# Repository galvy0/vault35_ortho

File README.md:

# Vault35 Ortho PCB
Ortho version of Cain's Vault35 keyboard.  
Check out the original product and other awesome projects of Cain at [https://mechvault.net/](https://mechvault.net/).  

### Current Progress
PCB has been tested and is good to go.  
Now working on plates.  

## PCB
### PCB Renders

### Layout Options

## Plate
Many plate configurations are possible depending on the use of the middle column.  
Various plate options can be found in plates folder.  
This is the most inclusive version, which supports every configuration except 3u stabs on macro column:  

## Firmware
https://github.com/galvy0/qmk_firmware/tree/galvy/keyboards/galvy/vault35_ortho

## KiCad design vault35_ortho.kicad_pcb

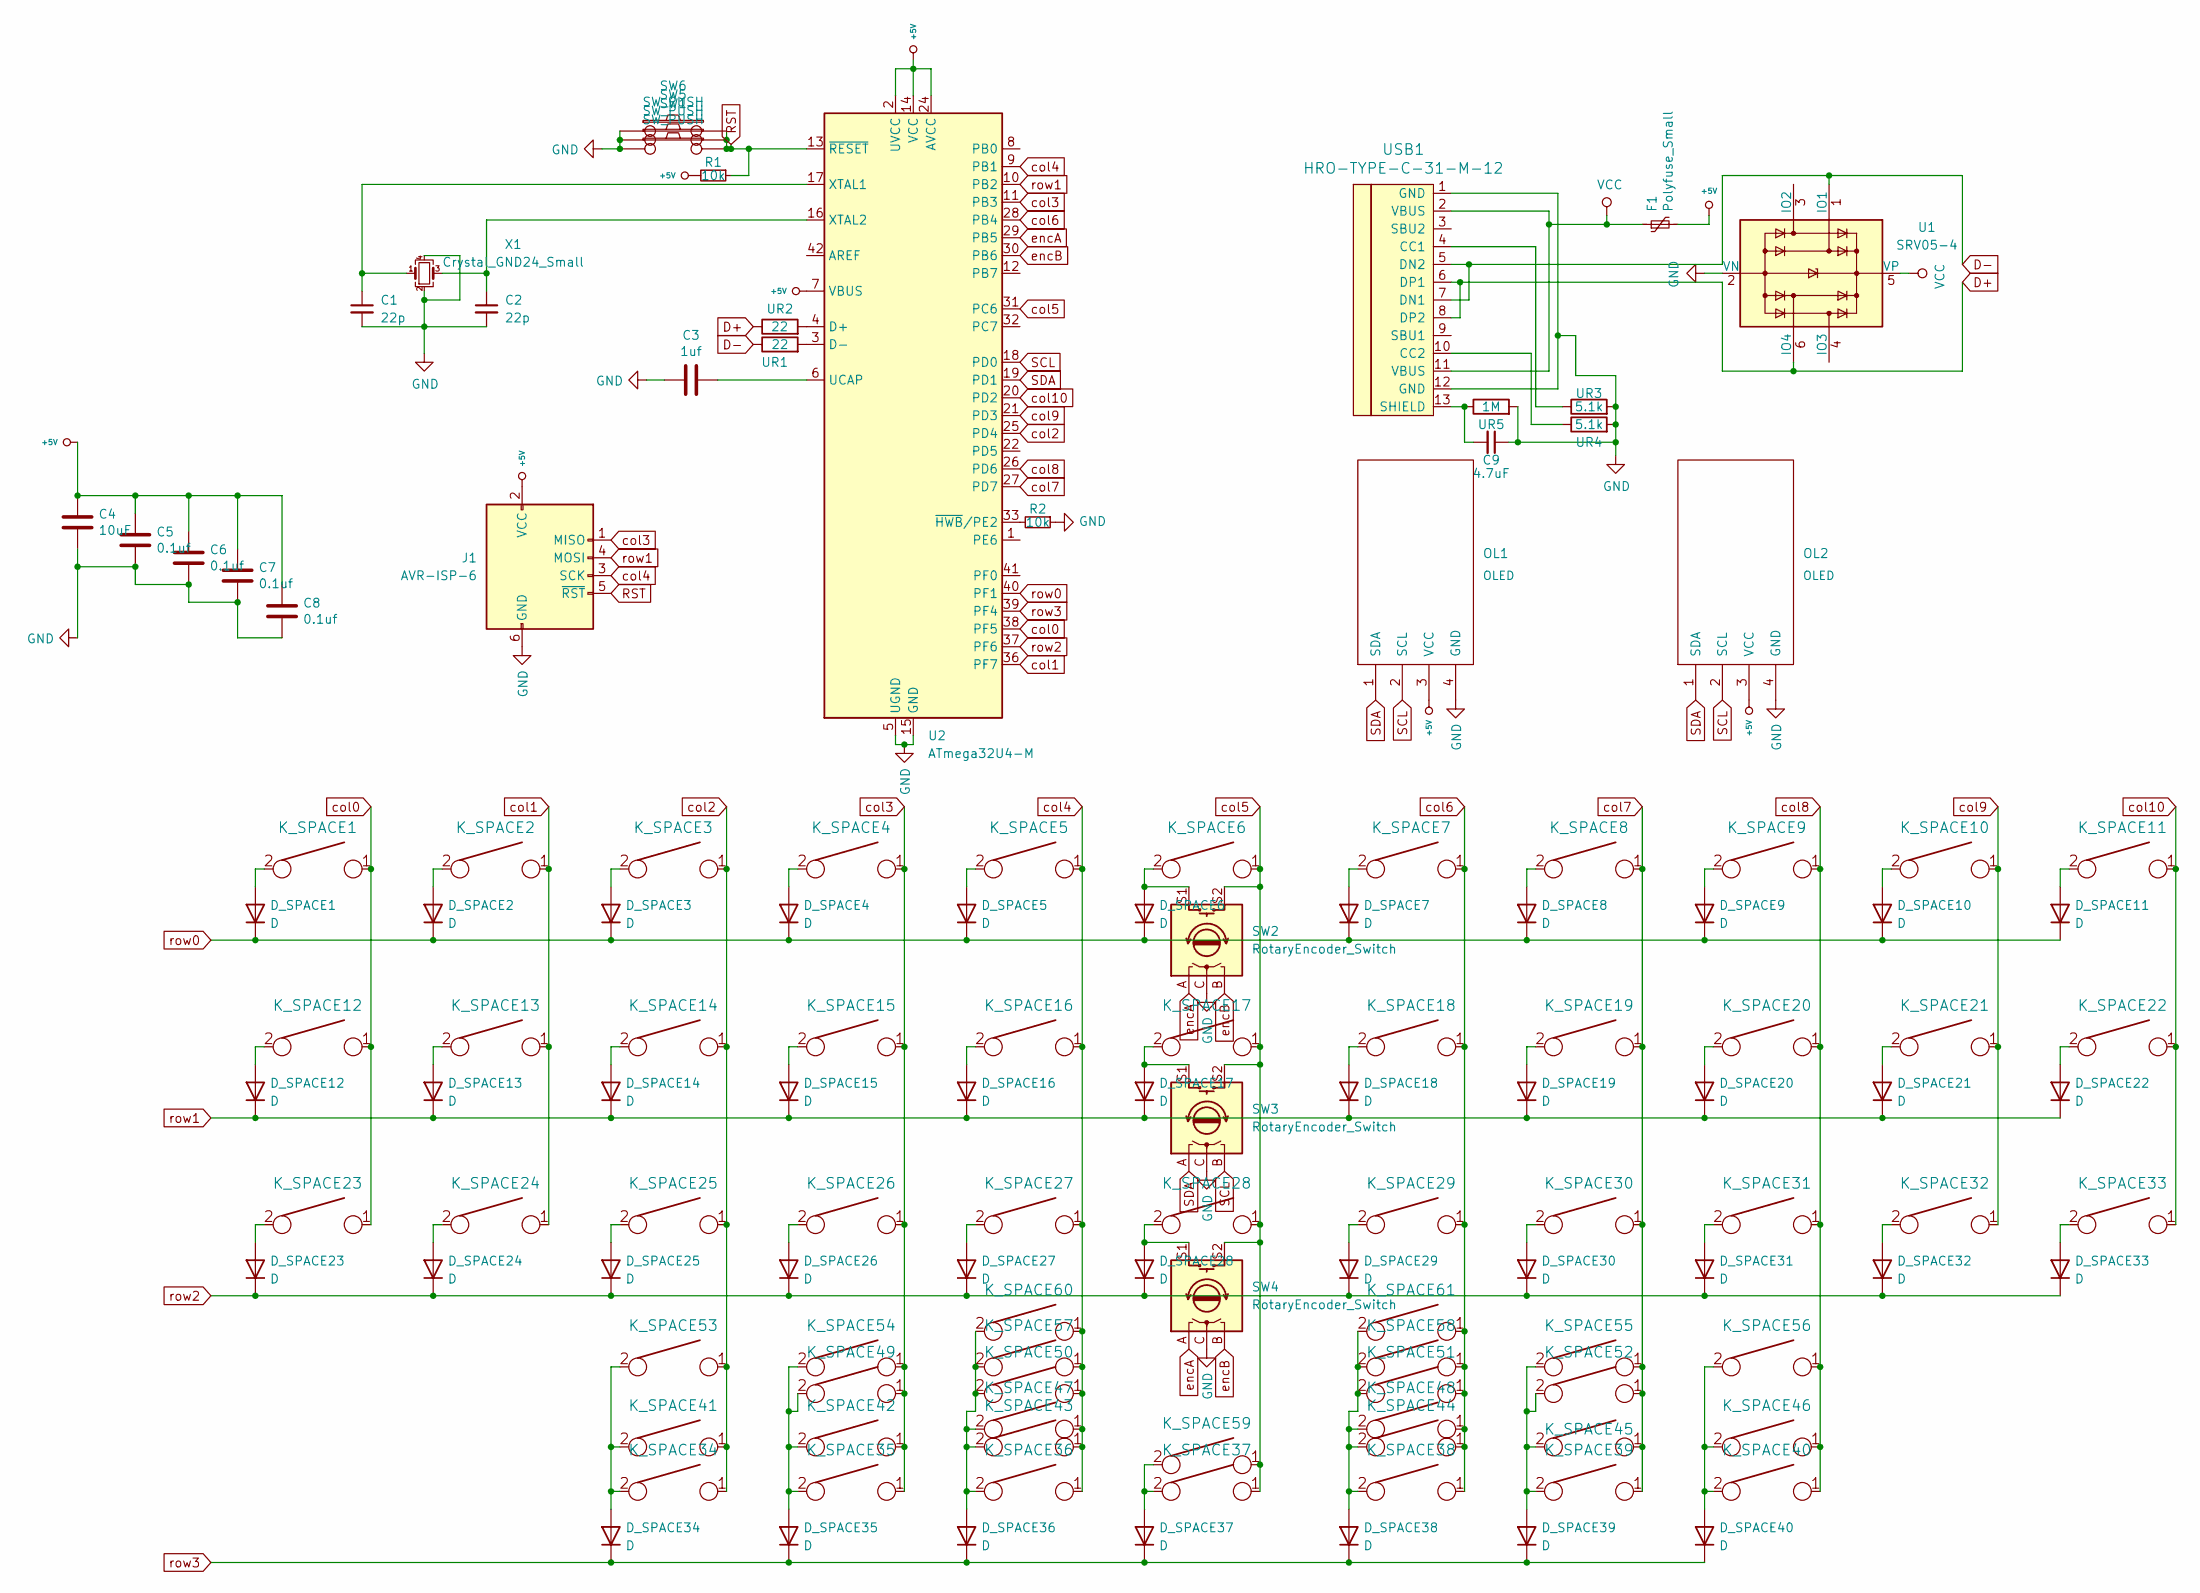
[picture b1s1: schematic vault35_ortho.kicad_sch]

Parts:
C1, C2: 22p; C_0805_2012Metric
C3: 1uf; C_0805_2012Metric
C4: 10uF; C_0805_2012Metric
C5, C6, C7, C8: 0.1uf; C_0805_2012Metric
C9: 4.7uF; C_0805_2012Metric
D_SPACE1, D_SPACE2, D_SPACE3, D_SPACE4, D_SPACE5, D_SPACE6, D_SPACE7, D_SPACE8, D_SPACE9, D_SPACE10, D_SPACE11, D_SPACE12, D_SPACE13, D_SPACE14, D_SPACE15, D_SPACE16, D_SPACE17, D_SPACE18, D_SPACE19, D_SPACE20, D_SPACE21, D_SPACE22, D_SPACE23, D_SPACE24, D_SPACE25, D_SPACE26, D_SPACE27, D_SPACE28, D_SPACE29, D_SPACE30, D_SPACE31, D_SPACE32, D_SPACE33, D_SPACE34, D_SPACE35, D_SPACE36, D_SPACE37, D_SPACE38, D_SPACE39, D_SPACE40: D; D_SOD-123
F1: Polyfuse_Small; Fuse_1206_3216Metric_Pad1.42x1.75mm_HandSolder
J1: AVR-ISP-6; IDC-Header_2x03_P2.54mm_Vertical
K_SPACE1, K_SPACE2, K_SPACE3, K_SPACE4, K_SPACE5, K_SPACE6, K_SPACE7, K_SPACE8, K_SPACE9, K_SPACE10, K_SPACE11, K_SPACE12, K_SPACE13, K_SPACE14, K_SPACE15, K_SPACE16, K_SPACE17, K_SPACE18, K_SPACE19, K_SPACE20, K_SPACE21, K_SPACE22, K_SPACE23, K_SPACE24, K_SPACE25, K_SPACE26, K_SPACE27, K_SPACE28, K_SPACE29, K_SPACE30, K_SPACE31, K_SPACE32, K_SPACE33, K_SPACE35, K_SPACE36, K_SPACE37, K_SPACE38, K_SPACE39, K_SPACE41, K_SPACE42, K_SPACE45, K_SPACE46: KEYSW; MXOnly-1U-NoLED
K_SPACE34, K_SPACE40, K_SPACE60, K_SPACE61: KEYSW; MXOnly-1.5U-NoLED
K_SPACE43, K_SPACE44: KEYSW; MXOnly-2U-ReversedStabilizers-NoLED
K_SPACE47: KEYSW; MXOnly-2.25U-ReversedStabilizers-NoLED
K_SPACE48: KEYSW; MXOnly-2.75U-ReversedStabilizers-NoLED
K_SPACE49, K_SPACE52, K_SPACE53, K_SPACE54, K_SPACE55, K_SPACE56: KEYSW; MXOnly-1.25U-NoLED
K_SPACE50, K_SPACE51: KEYSW; MXOnly-1.75U-NoLED
K_SPACE57, K_SPACE58, K_SPACE59: KEYSW; MXOnly-3U-ReversedStabilizers-NoLED
OL1, OL2: OLED; OLED_v2
R1, R2: 10k; R_0805_2012Metric
SW1, SW6: SW_PUSH; SW_SPST_SKQG_WithoutStem
SW2, SW3, SW4: RotaryEncoder_Switch; RotaryEncoder_Alps_EC11E-Switch_Vertical_H20mm
SW5: SW_PUSH; PinHeader_1x02_P2.54mm_Vertical
U1: SRV05-4; SOT-23-6
U2: ATmega32U4-M; QFN-44-1EP_7x7mm_P0.5mm_EP5.2x5.2mm
UR1, UR2: 22; R_0805_2012Metric
UR3, UR4: 5.1k; R_0805_2012Metric
UR5: 1M; R_0805_2012Metric
USB1: HRO-TYPE-C-31-M-12; HRO-TYPE-C-31-M-12-HandSoldering
X1: Crystal_GND24_Small; Crystal_SMD_3225-4Pin_3.2x2.5mm_HandSoldering

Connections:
+5V: C4.1, C5.1, C6.1, C7.1, C8.1, F1.2, J1.2 (VCC), OL1.3 (VCC), OL2.3 (VCC), R1.2, U2.2 (UVCC), U2.7 (VBUS), U2.14 (VCC), U2.24 (AVCC), U2.34 (VCC), U2.44 (AVCC)
D+: U1.6 (IO4), UR1.1, USB1.6 (DP1), USB1.8 (DP2)
D-: U1.1 (IO1), UR2.1, USB1.5 (DN2), USB1.7 (DN1)
GND: C1.2, C2.2, C3.2, C4.2, C5.2, C6.2, C7.2, C8.2, C9.1, J1.6 (GND), OL1.4 (GND), OL2.4 (GND), R2.1, SW1.1, SW2.C, SW3.C, SW4.C, SW5.1, SW6.1, U1.2 (VN), U2.5 (UGND), U2.15 (GND), U2.23 (GND), U2.35 (GND), U2.43 (GND), U2.45 (GND), UR3.2, UR4.2, UR5.2, USB1.1 (GND), USB1.12 (GND), X1.2, X1.4
unnamed: C1.1, U2.17 (XTAL1), X1.1
unnamed: C2.1, U2.16 (XTAL2), X1.3
unnamed: C3.1, U2.6 (UCAP)
unnamed: C9.2, UR5.1, USB1.13 (SHIELD)
unnamed: D_SPACE1.2 (A), K_SPACE1.2
unnamed: D_SPACE2.2 (A), K_SPACE2.2
unnamed: D_SPACE3.2 (A), K_SPACE3.2
unnamed: D_SPACE4.2 (A), K_SPACE4.2
unnamed: D_SPACE5.2 (A), K_SPACE5.2
unnamed: D_SPACE6.2 (A), K_SPACE6.2, SW2.S1
unnamed: D_SPACE7.2 (A), K_SPACE7.2
unnamed: D_SPACE8.2 (A), K_SPACE8.2
unnamed: D_SPACE9.2 (A), K_SPACE9.2
unnamed: D_SPACE10.2 (A), K_SPACE10.2
unnamed: D_SPACE11.2 (A), K_SPACE11.2
unnamed: D_SPACE12.2 (A), K_SPACE12.2
unnamed: D_SPACE13.2 (A), K_SPACE13.2
unnamed: D_SPACE14.2 (A), K_SPACE14.2
unnamed: D_SPACE15.2 (A), K_SPACE15.2
unnamed: D_SPACE16.2 (A), K_SPACE16.2
unnamed: D_SPACE17.2 (A), K_SPACE17.2, SW3.S1
unnamed: D_SPACE18.2 (A), K_SPACE18.2
unnamed: D_SPACE19.2 (A), K_SPACE19.2
unnamed: D_SPACE20.2 (A), K_SPACE20.2
unnamed: D_SPACE21.2 (A), K_SPACE21.2
unnamed: D_SPACE22.2 (A), K_SPACE22.2
unnamed: D_SPACE23.2 (A), K_SPACE23.2
unnamed: D_SPACE24.2 (A), K_SPACE24.2
unnamed: D_SPACE25.2 (A), K_SPACE25.2
unnamed: D_SPACE26.2 (A), K_SPACE26.2
unnamed: D_SPACE27.2 (A), K_SPACE27.2
unnamed: D_SPACE28.2 (A), K_SPACE28.2, SW4.S1
unnamed: D_SPACE29.2 (A), K_SPACE29.2
unnamed: D_SPACE30.2 (A), K_SPACE30.2
unnamed: D_SPACE31.2 (A), K_SPACE31.2
unnamed: D_SPACE32.2 (A), K_SPACE32.2
unnamed: D_SPACE33.2 (A), K_SPACE33.2
unnamed: D_SPACE34.2 (A), K_SPACE34.2, K_SPACE41.2, K_SPACE53.2
unnamed: D_SPACE35.2 (A), K_SPACE35.2, K_SPACE42.2, K_SPACE49.2, K_SPACE54.2
unnamed: D_SPACE36.2 (A), K_SPACE36.2, K_SPACE43.2, K_SPACE47.2, K_SPACE50.2, K_SPACE57.2, K_SPACE60.2
unnamed: D_SPACE37.2 (A), K_SPACE37.2, K_SPACE59.2
unnamed: D_SPACE38.2 (A), K_SPACE38.2, K_SPACE44.2, K_SPACE48.2, K_SPACE51.2, K_SPACE58.2, K_SPACE61.2
unnamed: D_SPACE39.2 (A), K_SPACE39.2, K_SPACE45.2, K_SPACE52.2, K_SPACE55.2
unnamed: D_SPACE40.2 (A), K_SPACE40.2, K_SPACE46.2, K_SPACE56.2
unnamed: R2.2, U2.33 (~HWB/PE2)
unnamed: U2.3 (D-), UR2.2
unnamed: U2.4 (D+), UR1.2
unnamed: UR3.1, USB1.4 (CC1)
unnamed: UR4.1, USB1.10 (CC2)
RST: J1.5 (~RST), R1.1, SW1.2, SW5.2, SW6.2, U2.13 (~RESET)
SCL: OL1.2 (SCL), OL2.2 (SCL), SW3.B, U2.18 (PD0)
SDA: OL1.1 (SDA), OL2.1 (SDA), SW3.A, U2.19 (PD1)
VCC: F1.1, U1.5 (VP), USB1.2 (VBUS), USB1.11 (VBUS)
col0: K_SPACE1.1, K_SPACE12.1, K_SPACE23.1, U2.38 (PF5)
col1: K_SPACE2.1, K_SPACE13.1, K_SPACE24.1, U2.36 (PF7)
col2: K_SPACE3.1, K_SPACE14.1, K_SPACE25.1, K_SPACE34.1, K_SPACE41.1, K_SPACE53.1, U2.25 (PD4)
col3: J1.1 (MISO), K_SPACE4.1, K_SPACE15.1, K_SPACE26.1, K_SPACE35.1, K_SPACE42.1, K_SPACE49.1, K_SPACE54.1, U2.11 (PB3)
col4: J1.3 (SCK), K_SPACE5.1, K_SPACE16.1, K_SPACE27.1, K_SPACE36.1, K_SPACE43.1, K_SPACE47.1, K_SPACE50.1, K_SPACE57.1, K_SPACE60.1, U2.9 (PB1)
col5: K_SPACE6.1, K_SPACE17.1, K_SPACE28.1, K_SPACE37.1, K_SPACE59.1, SW2.S2, SW3.S2, SW4.S2, U2.31 (PC6)
col6: K_SPACE7.1, K_SPACE18.1, K_SPACE29.1, K_SPACE38.1, K_SPACE44.1, K_SPACE48.1, K_SPACE51.1, K_SPACE58.1, K_SPACE61.1, U2.28 (PB4)
col7: K_SPACE8.1, K_SPACE19.1, K_SPACE30.1, K_SPACE39.1, K_SPACE45.1, K_SPACE52.1, K_SPACE55.1, U2.27 (PD7)
col8: K_SPACE9.1, K_SPACE20.1, K_SPACE31.1, K_SPACE40.1, K_SPACE46.1, K_SPACE56.1, U2.26 (PD6)
col9: K_SPACE10.1, K_SPACE21.1, K_SPACE32.1, U2.21 (PD3)
col10: K_SPACE11.1, K_SPACE22.1, K_SPACE33.1, U2.20 (PD2)
encA: SW2.A, SW4.A, U2.29 (PB5)
encB: SW2.B, SW4.B, U2.30 (PB6)
row0: D_SPACE1.1 (K), D_SPACE2.1 (K), D_SPACE3.1 (K), D_SPACE4.1 (K), D_SPACE5.1 (K), D_SPACE6.1 (K), D_SPACE7.1 (K), D_SPACE8.1 (K), D_SPACE9.1 (K), D_SPACE10.1 (K), D_SPACE11.1 (K), U2.40 (PF1)
row1: D_SPACE12.1 (K), D_SPACE13.1 (K), D_SPACE14.1 (K), D_SPACE15.1 (K), D_SPACE16.1 (K), D_SPACE17.1 (K), D_SPACE18.1 (K), D_SPACE19.1 (K), D_SPACE20.1 (K), D_SPACE21.1 (K), D_SPACE22.1 (K), J1.4 (MOSI), U2.10 (PB2)
row2: D_SPACE23.1 (K), D_SPACE24.1 (K), D_SPACE25.1 (K), D_SPACE26.1 (K), D_SPACE27.1 (K), D_SPACE28.1 (K), D_SPACE29.1 (K), D_SPACE30.1 (K), D_SPACE31.1 (K), D_SPACE32.1 (K), D_SPACE33.1 (K), U2.37 (PF6)
row3: D_SPACE34.1 (K), D_SPACE35.1 (K), D_SPACE36.1 (K), D_SPACE37.1 (K), D_SPACE38.1 (K), D_SPACE39.1 (K), D_SPACE40.1 (K), U2.39 (PF4)

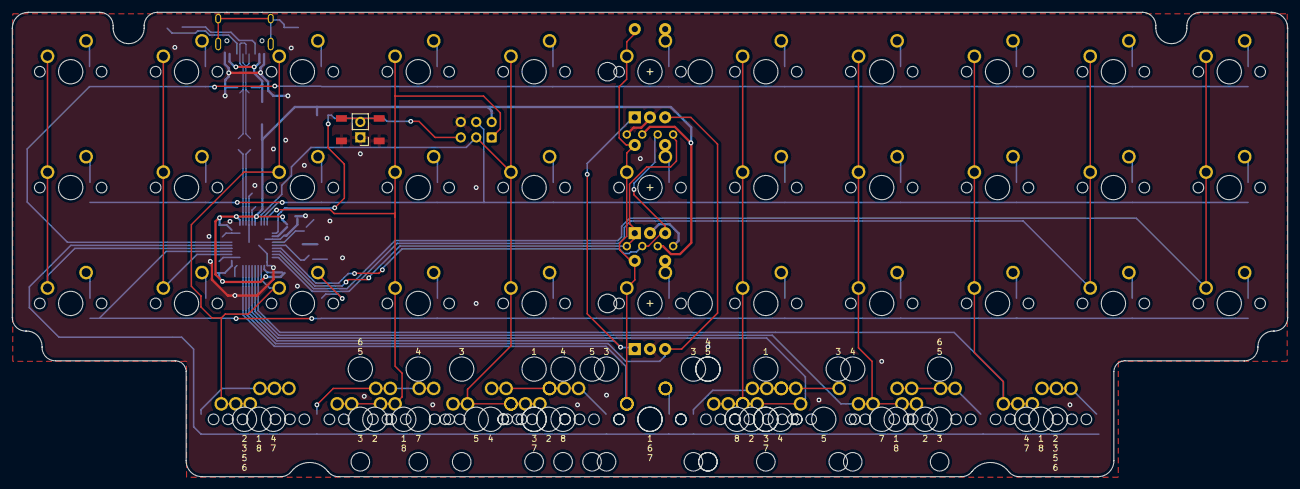
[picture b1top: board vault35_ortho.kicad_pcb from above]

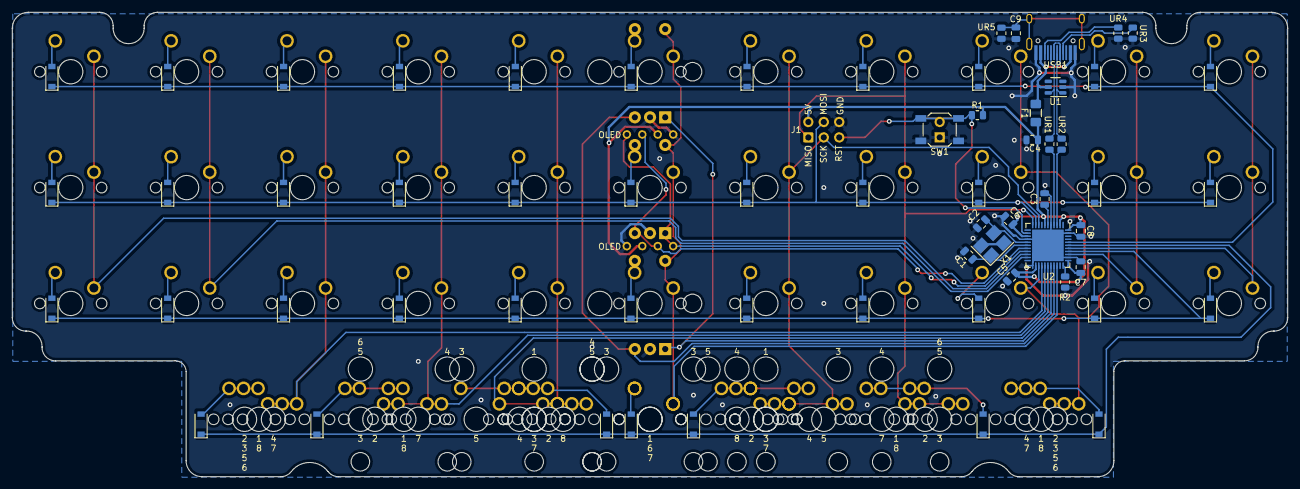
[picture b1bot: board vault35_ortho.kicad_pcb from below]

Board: 2 copper layers, 209.7 x 76.4 mm, 131 parts (63 on the bottom side), 74 nets.

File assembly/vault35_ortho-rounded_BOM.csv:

sep=;
"Id";"Designator";"Package";"Quantity";"Designation";"Supplier and ref";
1;"K_SPACE4,K_SPACE17,K_SPACE30,K_SPACE41,K_SPACE45,K_SPACE9,K_SPACE21,K_SPACE33,K_SPACE29,K_SPACE37,K_SPACE15,K_SPACE28,K_SPACE39,K_SPACE10,K_SPACE2,K_SPACE14,K_SPACE32,K_SPACE26,K_SPACE36,K_SPACE25,K_SPACE38,K_SPACE8,K_SPACE35,K_SPACE20,K_SPACE46,K_SPACE11,K_SPACE19,K_SPACE23,K_SPACE16,K_SPACE12,K_SPACE22,K_SPACE3,K_SPACE7,K_SPACE6,K_SPACE5,K_SPACE27,K_SPACE24,K_SPACE18,K_SPACE31,K_SPACE1,K_SPACE42,K_SPACE13";"MXOnly-1U-NoLED";42;"KEYSW";;;
2;"SW5";"PinHeader_1x02_P2.54mm_Vertical";1;"SW_PUSH";;;
3;"K_SPACE54,K_SPACE55,K_SPACE53,K_SPACE52,K_SPACE56,K_SPACE49";"MXOnly-1.25U-NoLED";6;"KEYSW";;;
4;"K_SPACE51,K_SPACE50";"MXOnly-1.75U-NoLED";2;"KEYSW";;;
5;"K_SPACE43,K_SPACE44";"MXOnly-2U-ReversedStabilizers-NoLED";2;"KEYSW";;;
6;"K_SPACE60,K_SPACE34,K_SPACE61,K_SPACE40";"MXOnly-1.5U-NoLED";4;"KEYSW";;;
7;"K_SPACE47";"MXOnly-2.25U-ReversedStabilizers-NoLED";1;"KEYSW";;;
8;"K_SPACE59,K_SPACE58,K_SPACE57";"MXOnly-3U-ReversedStabilizers-NoLED";3;"KEYSW";;;
9;"SW2,SW3,SW4";"RotaryEncoder_Alps_EC11E-Switch_Vertical_H20mm";3;"RotaryEncoder_Switch";;;
10;"SW6,SW1";"SW_SPST_SKQG_WithoutStem";2;"SW_PUSH";;;
11;"OL1,OL2";"OLED_v2";2;"OLED";;;
12;"K_SPACE48";"MXOnly-2.75U-ReversedStabilizers-NoLED";1;"KEYSW";;;
13;"D_SPACE17,D_SPACE34,D_SPACE5,D_SPACE1,D_SPACE32,D_SPACE36,D_SPACE38,D_SPACE25,D_SPACE18,D_SPACE9,D_SPACE13,D_SPACE35,D_SPACE12,D_SPACE29,D_SPACE2,D_SPACE20,D_SPACE24,D_SPACE21,D_SPACE15,D_SPACE26,D_SPACE16,D_SPACE14,D_SPACE30,D_SPACE4,D_SPACE11,D_SPACE37,D_SPACE10,D_SPACE40,D_SPACE8,D_SPACE39,D_SPACE3,D_SPACE27,D_SPACE28,D_SPACE23,D_SPACE31,D_SPACE7,D_SPACE33,D_SPACE19,D_SPACE22,D_SPACE6";"D_SOD-123";40;"D";;;
14;"X1";"Crystal_SMD_3225-4Pin_3.2x2.5mm_HandSoldering";1;"Crystal_GND24_Small";;;
15;"U1";"SOT-23-6";1;"SRV05-4";;;
16;"UR5";"R_0805_2012Metric";1;"1M";;;
17;"F1";"Fuse_1206_3216Metric_Pad1.42x1.75mm_HandSolder";1;"Polyfuse_Small";;;
18;"UR3,UR4";"R_0805_2012Metric";2;"5.1k";;;
19;"U2";"QFN-44-1EP_7x7mm_P0.5mm_EP5.2x5.2mm";1;"ATmega32U4-M";;;
20;"C2,C1";"C_0805_2012Metric";2;"22p";;;
21;"C4";"C_0805_2012Metric";1;"10uF";;;
22;"UR1,UR2";"R_0805_2012Metric";2;"22";;;
23;"R2,R1";"R_0805_2012Metric";2;"10k";;;
24;"C6,C8,C5,C7";"C_0805_2012Metric";4;"0.1uf";;;
25;"C3";"C_0805_2012Metric";1;"1uf";;;
26;"C9";"C_0805_2012Metric";1;"4.7uF";;;
27;"USB1";"HRO-TYPE-C-31-M-12-HandSoldering";1;"HRO-TYPE-C-31-M-12";;;
28;"J1";"IDC-Header_2x03_P2.54mm_Vertical";1;"AVR-ISP-6";;;

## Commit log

2022-06-15 init
2022-06-15 Update readme to contain current progress
2022-06-25 add firmware url
2022-06-25 update progress
2022-06-26 update oled related plate stuff
2022-08-29 update qmk url
